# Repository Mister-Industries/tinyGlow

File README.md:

# tinyGlow — Smart LED HAT for tinyCore ESP32-S3

<div align="center">

**A smart LED control HAT for the [tinyCore](https://github.com/Mister-Industries/tinyCore) ESP32-S3 platform.**

[Purchase](https://tinycore.cc/store/products/tinyGlow) · [Discord](https://discord.gg/hvJZhwfQsF) · [Documentation](https://docs.mr.industries)

</div>

---

### How to open the Schematic (KiCAD)

The tinyGlow design files are provided as a KiCAD project. KiCAD is a free, open-source PCB design tool.

To open the files:
1. Download and install [KiCAD](https://www.kicad.org/download/) (version 7.0 or later recommended).
2. Open KiCAD and click **File > Open Project** (or press Ctrl+O).
3. Navigate to the Hardware folder of this repository and select the `.kicad_pro` project file.
4. Once the project opens, you can access:
   - **Schematic Editor** - Double-click the `.kicad_sch` file to view the circuit design
   - **PCB Editor** - Double-click the `.kicad_pcb` file to view the board layout

The project will open with all associated files (schematic, PCB, and libraries) ready to view and edit.

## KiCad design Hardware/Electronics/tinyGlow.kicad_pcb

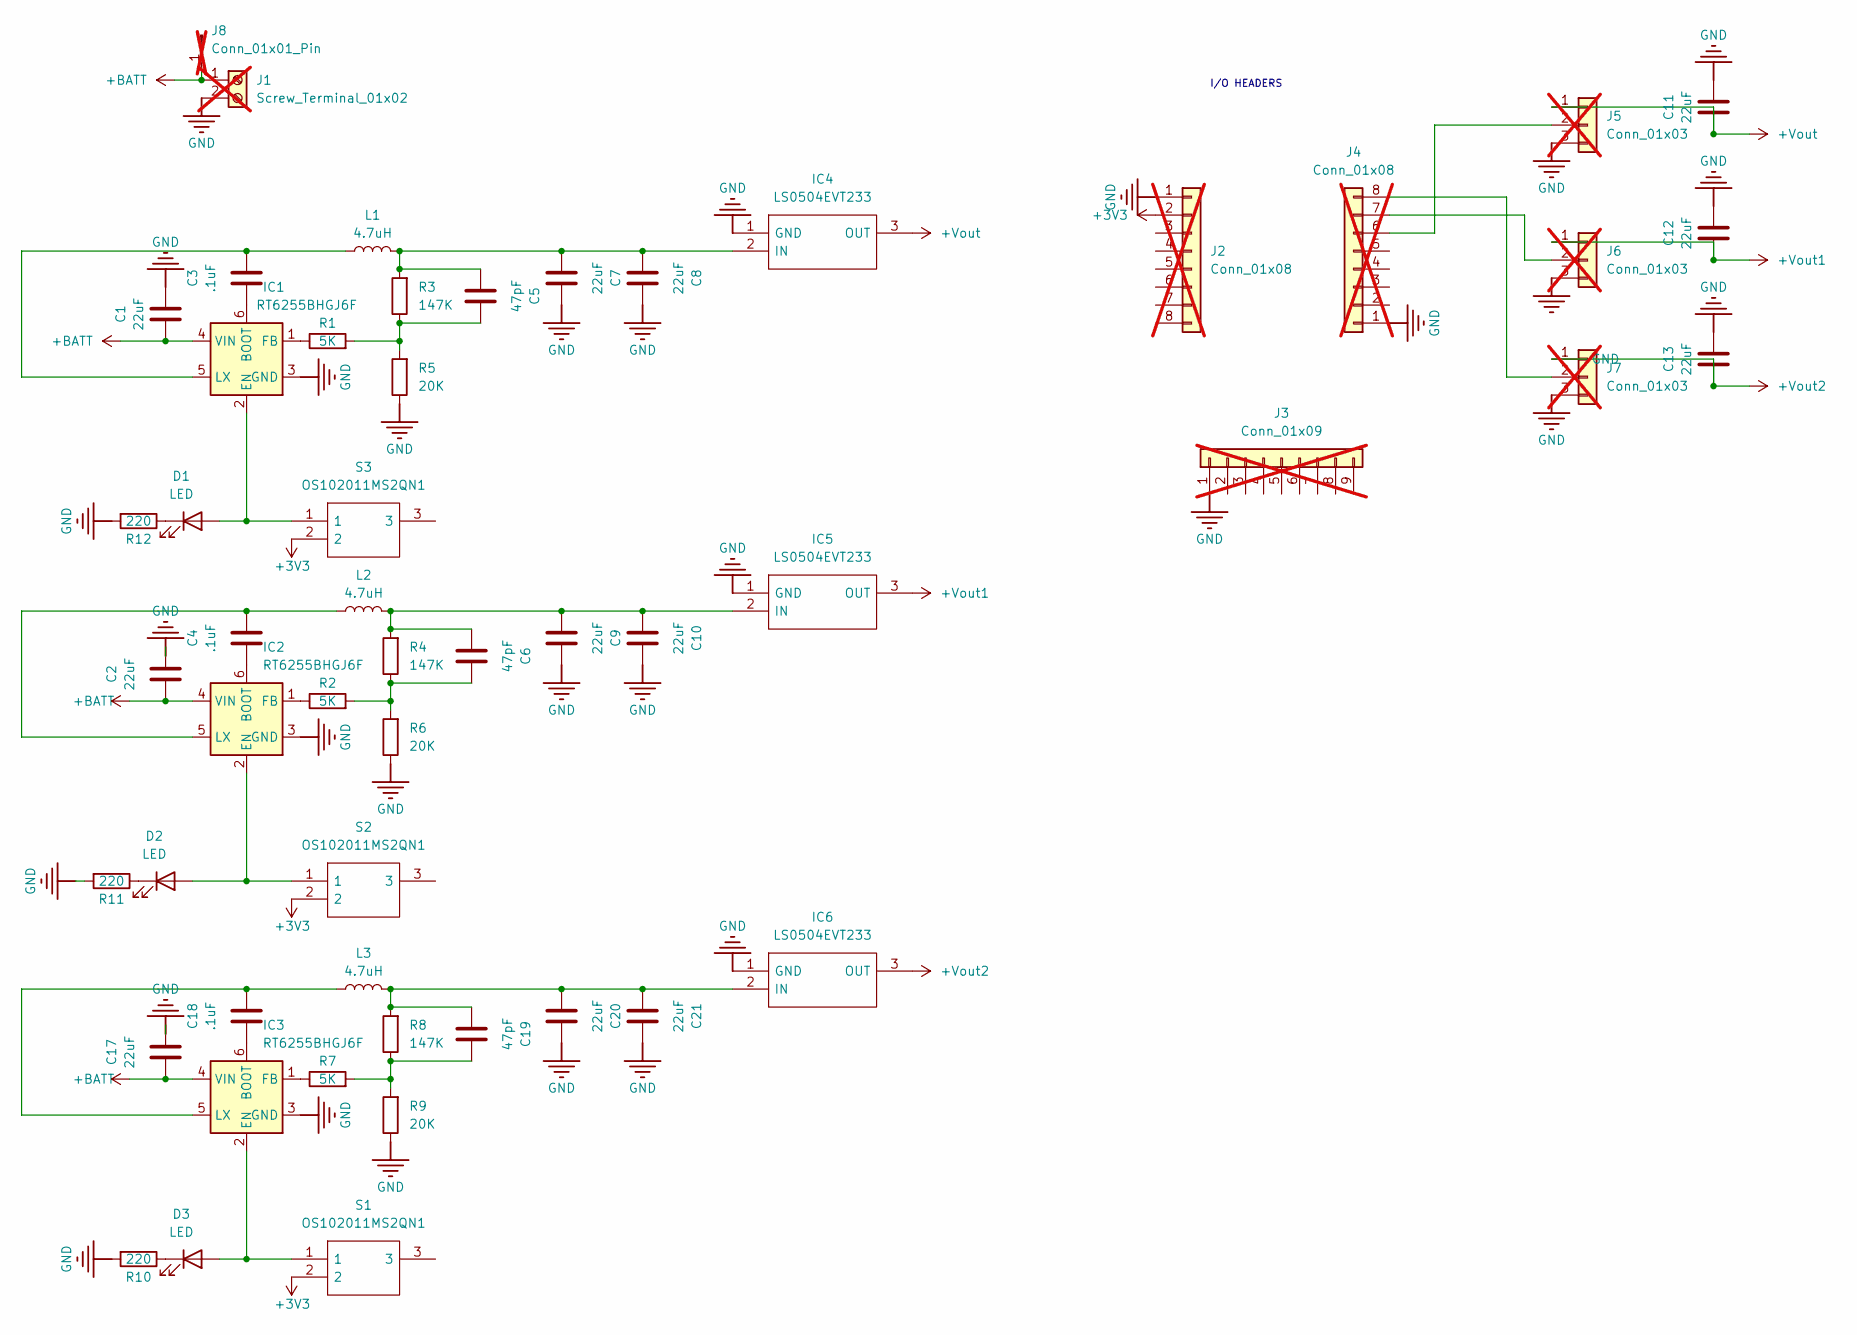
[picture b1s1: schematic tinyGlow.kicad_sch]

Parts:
C1, C2, C7, C8, C9, C10, C11, C12, C13, C17, C20, C21: 22uF; C_0603_1608Metric
C3, C4, C18: .1uF; C_0603_1608Metric
C5, C6, C19: 47pF; C_0603_1608Metric
D1, D2, D3: LED; D_0603_1608Metric
IC1, IC2, IC3: RT6255BHGJ6F; TSOT-23-6_HandSoldering
IC4, IC5, IC6: LS0504EVT233; TSOT-23; Mouser Part Number 576-LS0504EVT233
J1: Screw_Terminal_01x02; PinSocket_1x02_P2.54mm_Vertical; not fitted
J2, J4: Conn_01x08; PinHeader_1x08_P2.54mm_Vertical; not fitted
J3: Conn_01x09; PinHeader_1x09_P2.54mm_Vertical; not fitted
J5, J6, J7: Conn_01x03; PinHeader_1x03_P2.54mm_Vertical; not fitted
J8: Conn_01x01_Pin; PinHeader_1x01_P2.54mm_Vertical; not fitted
L1, L2, L3: 4.7uH; SPM6530T-4R7M
R1, R2, R7: 5K; R_0603_1608Metric
R3, R4, R8: 147K; R_0603_1608Metric
R5, R6, R9: 20K; R_0603_1608Metric
R10, R11, R12: 220; R_0603_1608Metric
S1, S2, S3: OS102011MS2QN1; OS102011MA1QN1; Mouser Part Number 611-OS102011MS2QN1

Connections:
+3V3: J2.2, S1.2, S2.2, S3.2
+BATT: C1.2, C2.1, C17.1, IC1.4 (VIN), IC2.4 (VIN), IC3.4 (VIN), J1.1, J8.1
+Vout: C11.2, IC4.3 (OUT), J5.1
+Vout1: C12.2, IC5.3 (OUT), J6.1
+Vout2: C13.2, IC6.3 (OUT), J7.1
GND: C1.1, C2.2, C7.2, C8.2, C9.2, C10.2, C11.1, C12.1, C13.1, C17.2, C20.2, C21.2, IC1.3 (GND), IC2.3 (GND), IC3.3 (GND), IC4.1 (GND), IC5.1 (GND), IC6.1 (GND), J1.2, J2.1, J3.1, J4.1, J5.3, J6.3, J7.3, R5.1, R6.1, R9.1, R10.2, R11.2, R12.2
unnamed: C5.2, R1.2, R3.1, R5.2
unnamed: C6.2, R2.2, R4.1, R6.2
unnamed: C19.2, R7.2, R8.1, R9.2
unnamed: D1.2 (A), IC1.2 (EN), S3.1
unnamed: D1.1 (K), R12.1
unnamed: D2.2 (A), IC2.2 (EN), S2.1
unnamed: D2.1 (K), R11.1
unnamed: D3.2 (A), IC3.2 (EN), S1.1
unnamed: D3.1 (K), R10.1
unnamed: C3.1, IC1.6 (BOOT)
unnamed: IC1.1 (FB), R1.1
unnamed: C3.2, IC1.5 (LX), L1.1
unnamed: C4.1, IC2.6 (BOOT)
unnamed: IC2.1 (FB), R2.1
unnamed: C4.2, IC2.5 (LX), L2.1
unnamed: C18.1, IC3.6 (BOOT)
unnamed: IC3.1 (FB), R7.1
unnamed: C18.2, IC3.5 (LX), L3.1
unnamed: C5.1, C7.1, C8.1, IC4.2 (IN), L1.2, R3.2
unnamed: C6.1, C9.1, C10.1, IC5.2 (IN), L2.2, R4.2
unnamed: C19.1, C20.1, C21.1, IC6.2 (IN), L3.2, R8.2
unnamed: J4.6, J5.2
unnamed: J4.7, J6.2
unnamed: J4.8, J7.2

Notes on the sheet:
I/O HEADERS

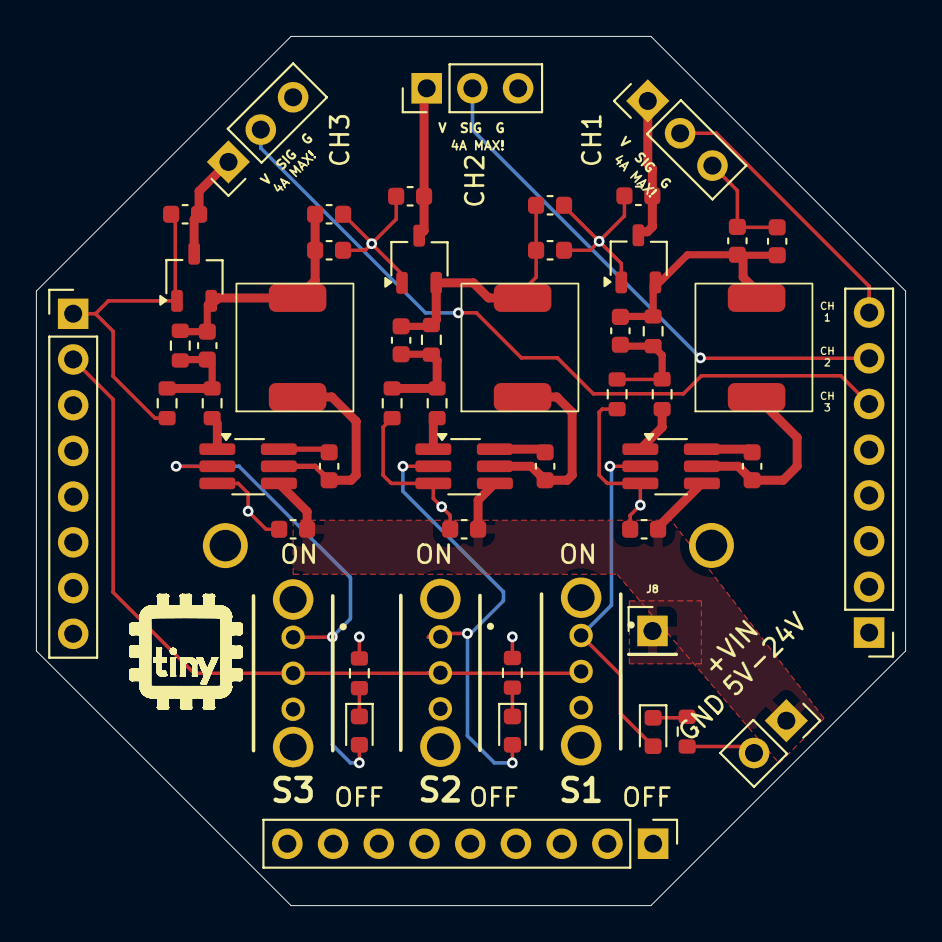
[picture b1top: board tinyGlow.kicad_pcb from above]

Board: 2 copper layers, 48.3 x 48.3 mm, 53 parts (0 on the bottom side), 30 nets.

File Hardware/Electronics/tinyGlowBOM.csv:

"Reference","Value","Datasheet","Footprint","Qty","DNP"
"C1,C2,C7,C8,C9,C10,C11,C12,C13,C17,C20,C21","22uF","~","Capacitor_SMD:C_0603_1608Metric","12",""
"C3,C4,C18",".1uF","~","Capacitor_SMD:C_0603_1608Metric","3",""
"C5,C6,C19","47pF","~","Capacitor_SMD:C_0603_1608Metric","3",""
"D1,D2,D3","LED","~","Diode_SMD:D_0603_1608Metric","3",""
"IC1,IC2,IC3","RT6255BHGJ6F","","Package_TO_SOT_SMD:TSOT-23-6_HandSoldering","3",""
"IC4,IC5,IC6","LS0504EVT233","https://www.mouser.in/datasheet/2/240/Littelfuse-3045601.pdf","Package_TO_SOT_SMD:TSOT-23","3",""
"L1,L2,L3","4.7uH","~","LibrarySPM6530T:SPM6530T-4R7M","3",""
"R1,R2,R7","5K","~","Resistor_SMD:R_0603_1608Metric","3",""
"R3,R4,R8","147K","~","Resistor_SMD:R_0603_1608Metric","3",""
"R5,R6,R9","20K","~","Resistor_SMD:R_0603_1608Metric","3",""
"R10,R11,R12","220","~","Resistor_SMD:R_0603_1608Metric","3",""
"S1,S2,S3","OS102011MS2QN1","https://www.ckswitches.com/media/1428/os.pdf","logos.preety:OS102011MA1QN1","3",""

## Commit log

2026-02-21 Adds photos and KiCAD schematics
2026-02-21 Added GPLV3.0 License
2026-02-21 Revise README with KiCAD details
    Updated project description and added installation instructions for KiCAD.
2026-02-21 Change tinyGlow Projects image in README
    Updated the image for tinyGlow Projects in the README.
2026-02-21 Revise README for tinyGlow project description
    Updated project description and title to reflect new functionality.
2026-02-21 Updated tinyGlow Schematics

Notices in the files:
README.md:
License: GPL v3
